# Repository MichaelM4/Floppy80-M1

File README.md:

########################################################################

Floppy 80 for the TRS-80 Model I

The Floppy80-M1 emulates the following features of the Expansion Interface
- 32k RAM expansion
- Up to 3 floppy drives
  - 1 and 2 sided
  - single and double density
  - up to 90 cylinders
- Up to 2 hard drives

Configuration of the Floppy80-M1 is performed with the placement of
files on the SD-Card inserted in its card reader.
The files are as follows:

system.cfg
- specifies system level options.  These are option that are not dependent
  of the ini file loaded.

  cfg options
  - Mem  - 0 = disable upper memory; 1 = enable upper memory;
           if not specified upper memory is enabled by default.
  - Wait - 0 = disable bus wait states; 1 = enable bus wait states.
           if not specified wait states are disabled by default.
  - Vhd  - 0 = disable hard disk emulation; 1 = enable hard disk emulation;
           if not specified hard disk emulation is enabled by default.

boot.cfg
- specified the default ini file to load at reset of the Floppy80
  when the floppy 80 boots or is reset it reads the contents of
  the boot.cfg to determine the default configuration ini file.

ini files
- specifies the disk images and options after reset.

  ini options
  - Drive0  - specified the image to load for drive :0
  - Drive1  - specified the image to load for drive :1
  - Drive2  - specified the image to load for drive :2
  - HD0     - specifies the image to load for tyhe first hard drive
  - HD1     - specifies the image to load for tyhe second hard drive
  - Doubler - 1 = doubler is enabled; 0 = doubler is disabled;

dmk files
- these are virtual disk images with a specific file format
  that allows them to be generated and used with a number
  of existing programs and simulators.

virtual hard drive images
- these are virtual hard drive images with a specific file format.
  They are used by the FreHD and TRS80-GP.

########################################################################

FDC utility
- Is a utility to interact with the Floppy80 from within the
  TRS-80 Model I operating environment.  Versions of FDC exist
  for the following operating systems

  - CPM 1.4.1 (Lifeboat)
  - CPM 1.5 (FMG)
  - Double DOS 4.2.4
  - DOS Plus 3.50
  - LDOS 5.3.1
  - MultiDOS 4.01
  - NEWDOS 3.0
  - NEWDOS 80 V2.0
  - TRSDOS 2.3
  - UltraDOS 4.2.0
  - VTDOS 3.0.0
  - VTDOS 4.0.1

  FDC.COM is used with the two CP/M OSs and
  FDC/CMD is used with the rest.

  Usage

  FDC OPT PARM1:drive

  Where:
  - OPT is one of the following
    - STA - returns the status of the Floppy80.
    - DIR - displays a list of file in the root folder of the SD-Card.
    - INI - switches between tyhe differnt ini file on the SD-Card.
    - DMK - allows the mounting of DMK disk images in the root folder
            of the SD-Card for a specified drive (0, 1 or 2).
    - FOR - copies a DMK disk image from the FOR folder of the SD-Card
            to one of the mounted disk images (0, 1 or 2).
    - IMP - imports a file from the root folder of the SD-Card
            into one of the mounted disk images (0, 1 or 2).

  FDC STA
  - Displays the contents to the ini file specified by boot.cfg

  FDC DIR filter
  - Displays a list of files in the root folder of the SD-Card.
    If filter is specified only files contain the filter character
    sequence are displayed.  If filter is not specified all files
    are displayed.

  FDC INI filename.exe
  - filename.exe is optional.  If not specified and list of ini files
    on the SD-Card will be displayed allow you to select the one to
    write to boot.cfg.  When specified FDC will bypass the file
    selection process.

  FDC DMK filename.exe n
  - filename.exe:n is optional.  When specified it will mount
    the dmk file names by filename.exe into the drive specified
    by n.  For example

    FDC DMK LDOS-DATA.DMK 2

    will mount the dmk file LDOS-DATA.DMK into drive :2

    If filename.exe:n is not specfied a list of dmk files
    will be listed allowing you to select on and the drive
    to mount it into.

  FDC FOR
  - list the files contained in the FMT folder of the SD-Card
    from which you can select one and specify the drive image
    to replace with it.  This is useful to generate blank disk
    images.

  FDC IMP filename.exe:n
  - imports the specified file from the root folder of the
    FAT32 formatted SD-Card to the disk image indicated by n.

########################################################################

Building Source
- Floppy80 firmware
  - Uses VSCode and the Pi Pico extension.

- FDC TRS (utility for the TRSDOS related utility)
  
  - zmac fdc.asm
  - use TRS80GP to import FDC/CMD onto a disk image
    
    - trs80gp -m1 -vs -frehd -frehd_dir zout -turbo -mem 48 -d0 dmk\ld531-0.dmk -d1 dmk\ld531-1.dmk -i "IMPORT2 FDC.CMD FDC/CMD:1\r"

- FDC CP/M (utility for the CP/M related utility)
  1. Compile program into a hex file.
  
       zmac fdc.asm
     
  2. Run TRS80GP loading the CP/M disk images.
     
       start trs80gp -m1 -vs -frehd -frehd_dir zout -turbo -mem 48 -d0 CPM141-0.dmk -d1 CPM141-1.dmk -d2 CPM141-2.dmk
     
  3. Select Load from TRS80GP File menu and select the hex file.
  
  4. Run "SAVE 20 B:FDC.COM" to save program memory contents to a .com file.
     As the program grows you will need to increase the value after SAVE.

     SAVE n ufn cr
     
       n   - number of 256-byte pages to be saved.
     
       ufn - unambiguous file name.
     
       cr  - carriage return.

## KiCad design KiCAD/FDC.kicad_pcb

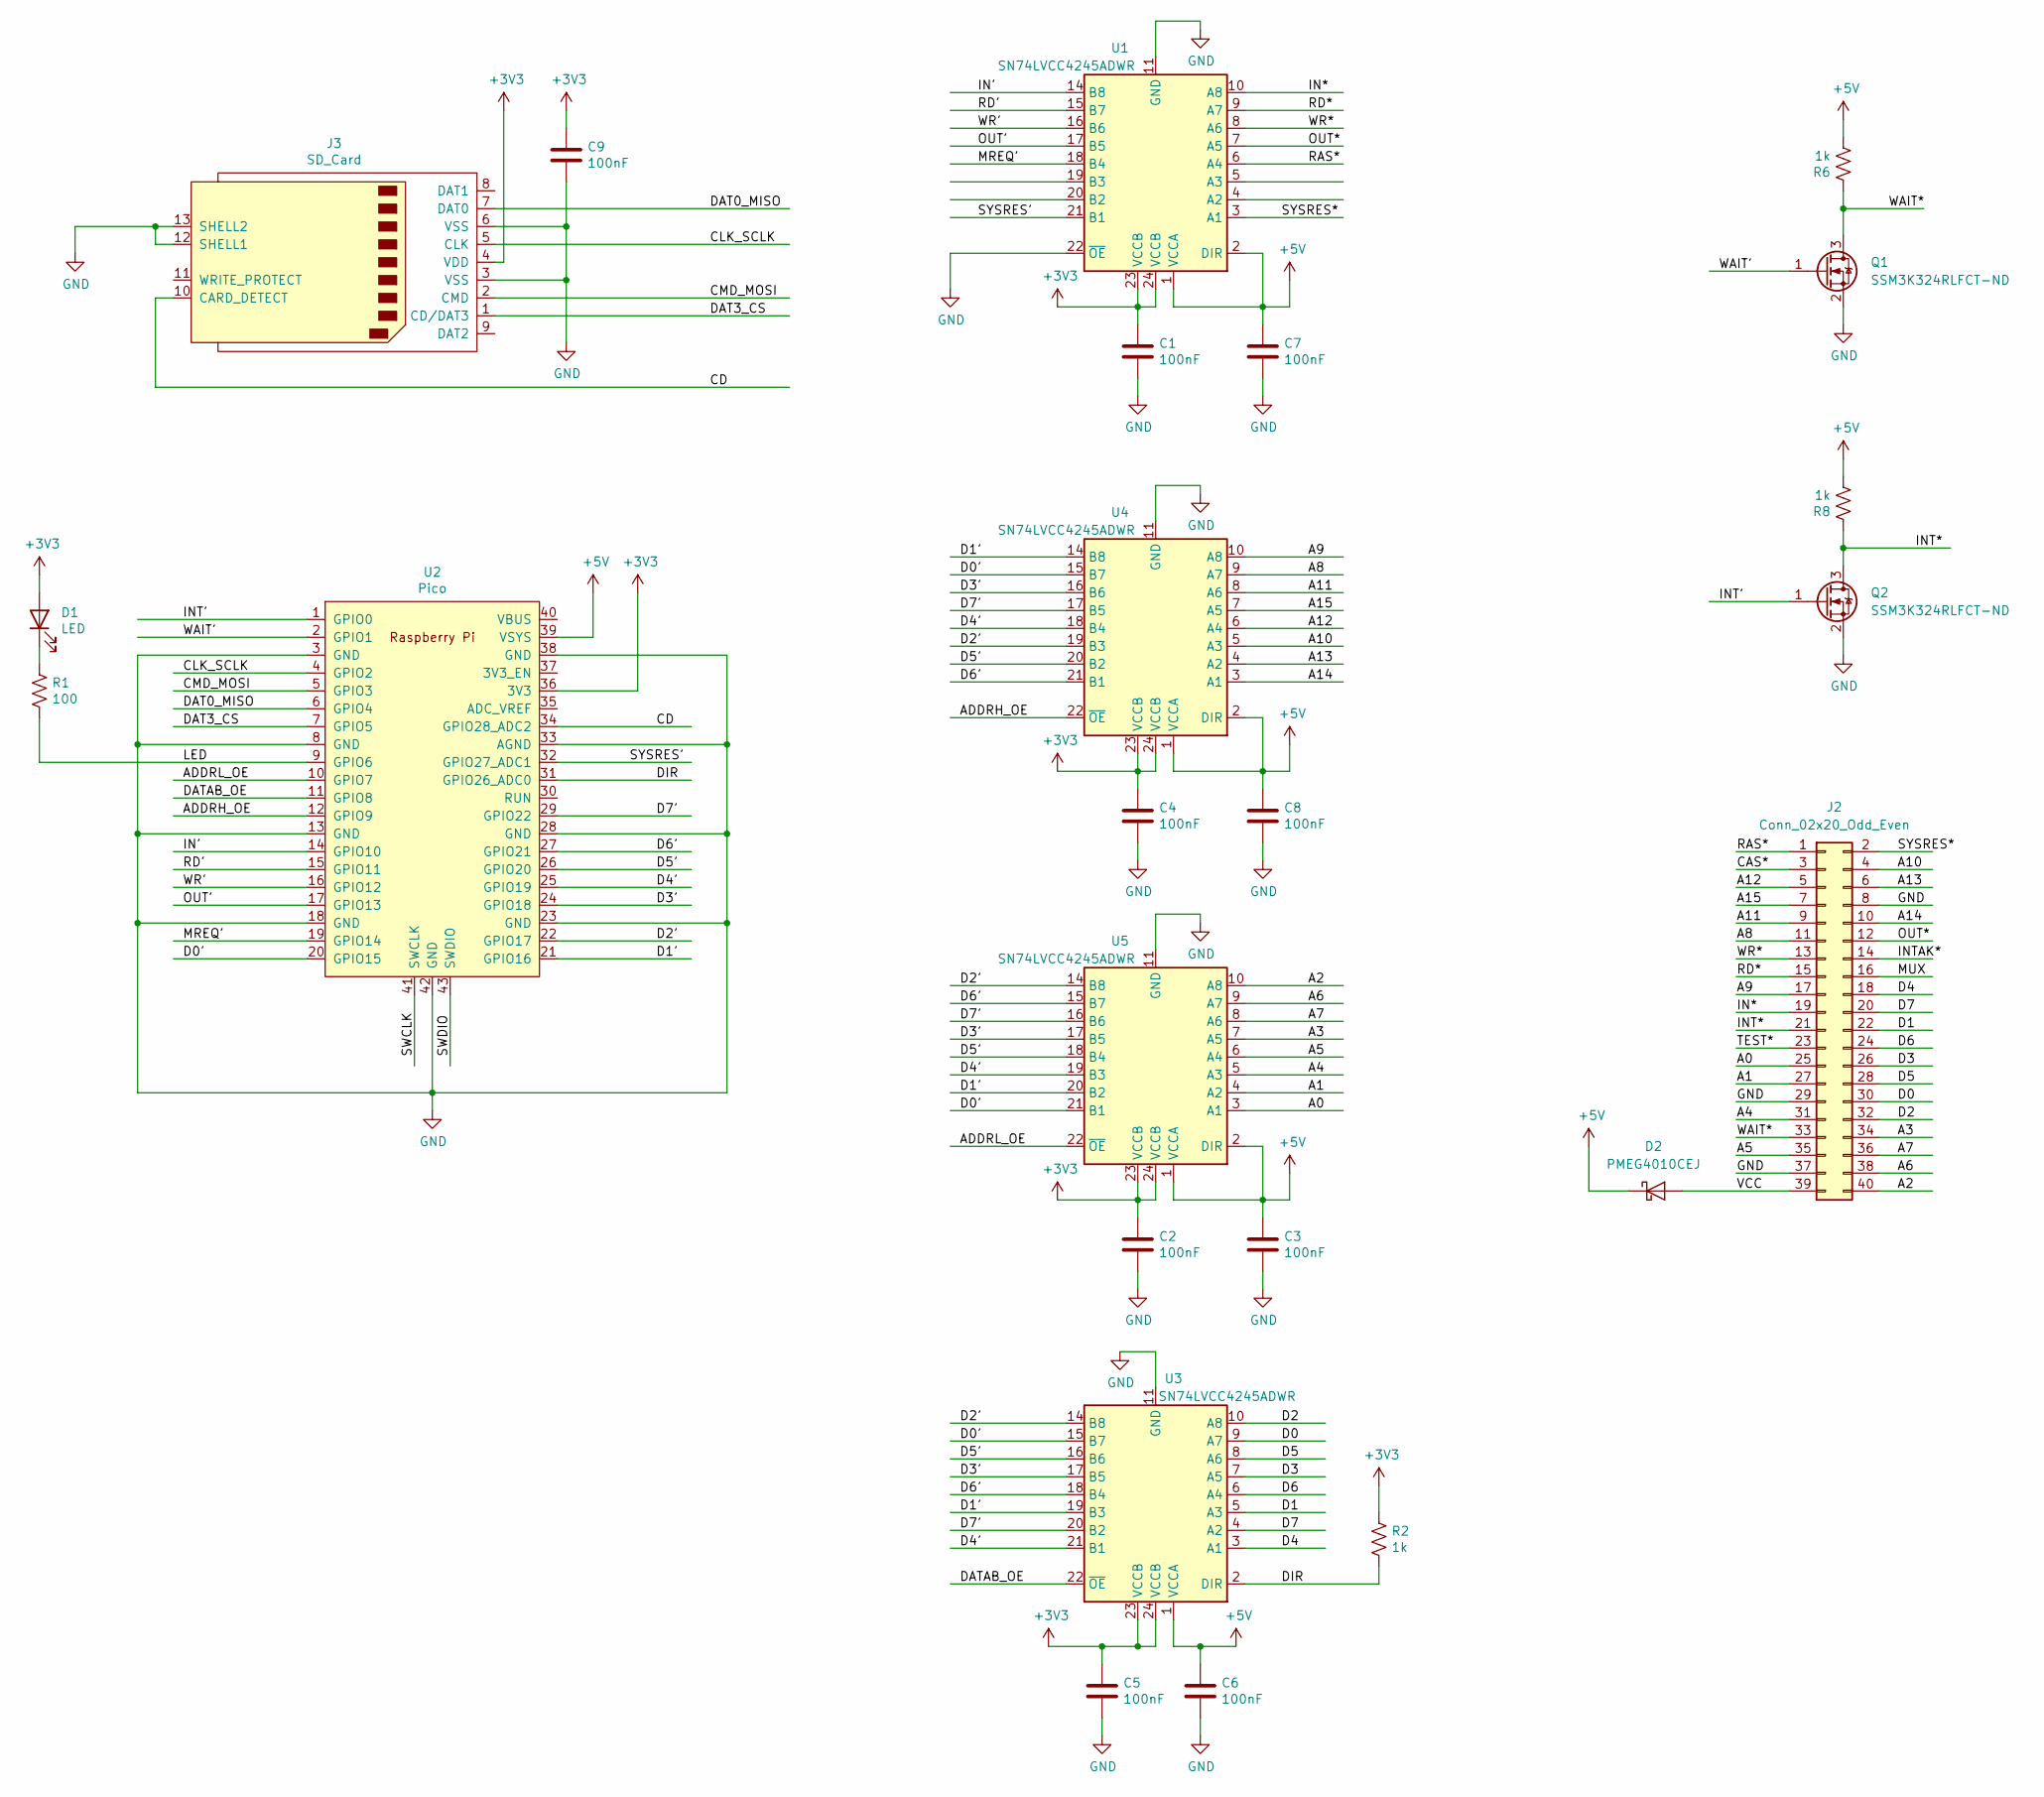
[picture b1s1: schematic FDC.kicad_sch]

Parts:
C1, C2, C3, C4, C5, C6, C7, C8, C9: 100nF; C_0805_2012Metric_Pad1.18x1.45mm_HandSolder; Digikey 732-8080-1-ND
D1: LED; LED_2816_7142Metric_Pad3.20x4.45mm_HandSolder; Digikey 754-1519-1-ND
D2: PMEG4010CEJ; D_SOD-323F
J2: Conn_02x20_Odd_Even; PinSocket_2x20_P2.54mm_Vertical; Part A31723-ND; Digikey A31723-ND
J3: SD_Card; SD_Kyocera_145638009511859+; Digikey 609-3956-1-ND
Q1, Q2: SSM3K324RLFCT-ND; SOT-23_Handsoldering; Digikey SSM3K324RLFCT-ND
R1: 100; R_0805_2012Metric_Pad1.20x1.40mm_HandSolder; Digikey RMCF0805FT100RCT-ND
R2, R6, R8: 1k; R_0805_2012Metric_Pad1.20x1.40mm_HandSolder; Digikey A106056CT-ND
U1, U3, U4, U5: SN74LVCC4245ADWR; SOIC-24W_7.5x15.4mm_P1.27mm; Digikey 296-26634-1-ND
U2: Pico; RPi_Pico_SMD_TH; Digikey 2648-SC0915CT-ND

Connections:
+3V3: C1.1, C2.1, C4.1, C5.1, C9.1, D1.2 (A), J3.4 (VDD), R2.1, U1.23 (VCCB), U1.24 (VCCB), U2.36 (3V3), U3.23 (VCCB), U3.24 (VCCB), U4.23 (VCCB), U4.24 (VCCB), U5.23 (VCCB), U5.24 (VCCB)
+5V: C3.1, C6.1, C7.1, C8.1, D2.1 (K), R6.2, R8.2, U1.1 (VCCA), U1.2 (DIR), U2.39 (VSYS), U3.1 (VCCA), U4.1 (VCCA), U4.2 (DIR), U5.1 (VCCA), U5.2 (DIR)
/A0: J2.25, U5.3 (A1)
/A1: J2.27, U5.4 (A2)
/A2: J2.40, U5.10 (A8)
/A3: J2.34, U5.7 (A5)
/A4: J2.31, U5.5 (A3)
/A5: J2.35, U5.6 (A4)
/A6: J2.38, U5.9 (A7)
/A7: J2.36, U5.8 (A6)
/A8: J2.11, U4.9 (A7)
/A9: J2.17, U4.10 (A8)
/A10: J2.4, U4.5 (A3)
/A11: J2.9, U4.8 (A6)
/A12: J2.5, U4.6 (A4)
/A13: J2.6, U4.4 (A2)
/A14: J2.10, U4.3 (A1)
/A15: J2.7, U4.7 (A5)
/ADDRH_OE: U2.12 (GPIO9), U4.22 (~OE)
/ADDRL_OE: U2.10 (GPIO7), U5.22 (~OE)
/CAS*: J2.3
/CD: J3.10 (CARD_DETECT), U2.34 (GPIO28_ADC2)
/CLK_SCLK: J3.5 (CLK), U2.4 (GPIO2)
/CMD_MOSI: J3.2 (CMD), U2.5 (GPIO3)
/D0: J2.30, U3.9 (A7)
/D0': U2.20 (GPIO15), U3.15 (B7), U4.15 (B7), U5.21 (B1)
/D1: J2.22, U3.5 (A3)
/D1': U2.21 (GPIO16), U3.19 (B3), U4.14 (B8), U5.20 (B2)
/D2: J2.32, U3.10 (A8)
/D2': U2.22 (GPIO17), U3.14 (B8), U4.19 (B3), U5.14 (B8)
/D3: J2.26, U3.7 (A5)
/D3': U2.24 (GPIO18), U3.17 (B5), U4.16 (B6), U5.17 (B5)
/D4: J2.18, U3.3 (A1)
/D4': U2.25 (GPIO19), U3.21 (B1), U4.18 (B4), U5.19 (B3)
/D5: J2.28, U3.8 (A6)
/D5': U2.26 (GPIO20), U3.16 (B6), U4.20 (B2), U5.18 (B4)
/D6: J2.24, U3.6 (A4)
/D6': U2.27 (GPIO21), U3.18 (B4), U4.21 (B1), U5.15 (B7)
/D7: J2.20, U3.4 (A2)
/D7': U2.29 (GPIO22), U3.20 (B2), U4.17 (B5), U5.16 (B6)
/DAT0_MISO: J3.7 (DAT0), U2.6 (GPIO4)
/DAT3_CS: J3.1 (CD/DAT3), U2.7 (GPIO5)
/DATAB_OE: U2.11 (GPIO8), U3.22 (~OE)
/DIR: R2.2, U2.31 (GPIO26_ADC0), U3.2 (DIR)
/IN': U1.14 (B8), U2.14 (GPIO10)
/IN*: J2.19, U1.10 (A8)
/INT': Q2.1 (G), U2.1 (GPIO0)
/INT*: J2.21, Q2.3 (D), R8.1
/INTAK*: J2.14
/LED: R1.2, U2.9 (GPIO6)
/MREQ': U1.18 (B4), U2.19 (GPIO14)
/MUX: J2.16
/OUT': U1.17 (B5), U2.17 (GPIO13)
/OUT*: J2.12, U1.7 (A5)
/RAS*: J2.1, U1.6 (A4)
/RD': U1.15 (B7), U2.15 (GPIO11)
/RD*: J2.15, U1.9 (A7)
/SWCLK: U2.41 (SWCLK)
/SWDIO: U2.43 (SWDIO)
/SYSRES': U1.21 (B1), U2.32 (GPIO27_ADC1)
/SYSRES*: J2.2, U1.3 (A1)
/TEST*: J2.23
/VCC: D2.2 (A), J2.39
/WAIT': Q1.1 (G), U2.2 (GPIO1)
/WAIT*: J2.33, Q1.3 (D), R6.1
/WR': U1.16 (B6), U2.16 (GPIO12)
/WR*: J2.13, U1.8 (A6)
GND: C1.2, C2.2, C3.2, C4.2, C5.2, C6.2, C7.2, C8.2, C9.2, J2.8, J2.29, J2.37, J3.3 (VSS), J3.6 (VSS), J3.12 (SHELL1), J3.13 (SHELL2), Q1.2 (S), Q2.2 (S), U1.11 (GND), U1.12 (GND), U1.13 (GND), U1.22 (~OE), U2.3 (GND), U2.8 (GND), U2.13 (GND), U2.18 (GND), U2.23 (GND), U2.28 (GND), U2.33 (AGND), U2.38 (GND), U2.42 (GND), U3.11 (GND), U3.12 (GND), U3.13 (GND), U4.11 (GND), U4.12 (GND), U4.13 (GND), U5.11 (GND), U5.12 (GND), U5.13 (GND)
unnamed: D1.1 (K), R1.1

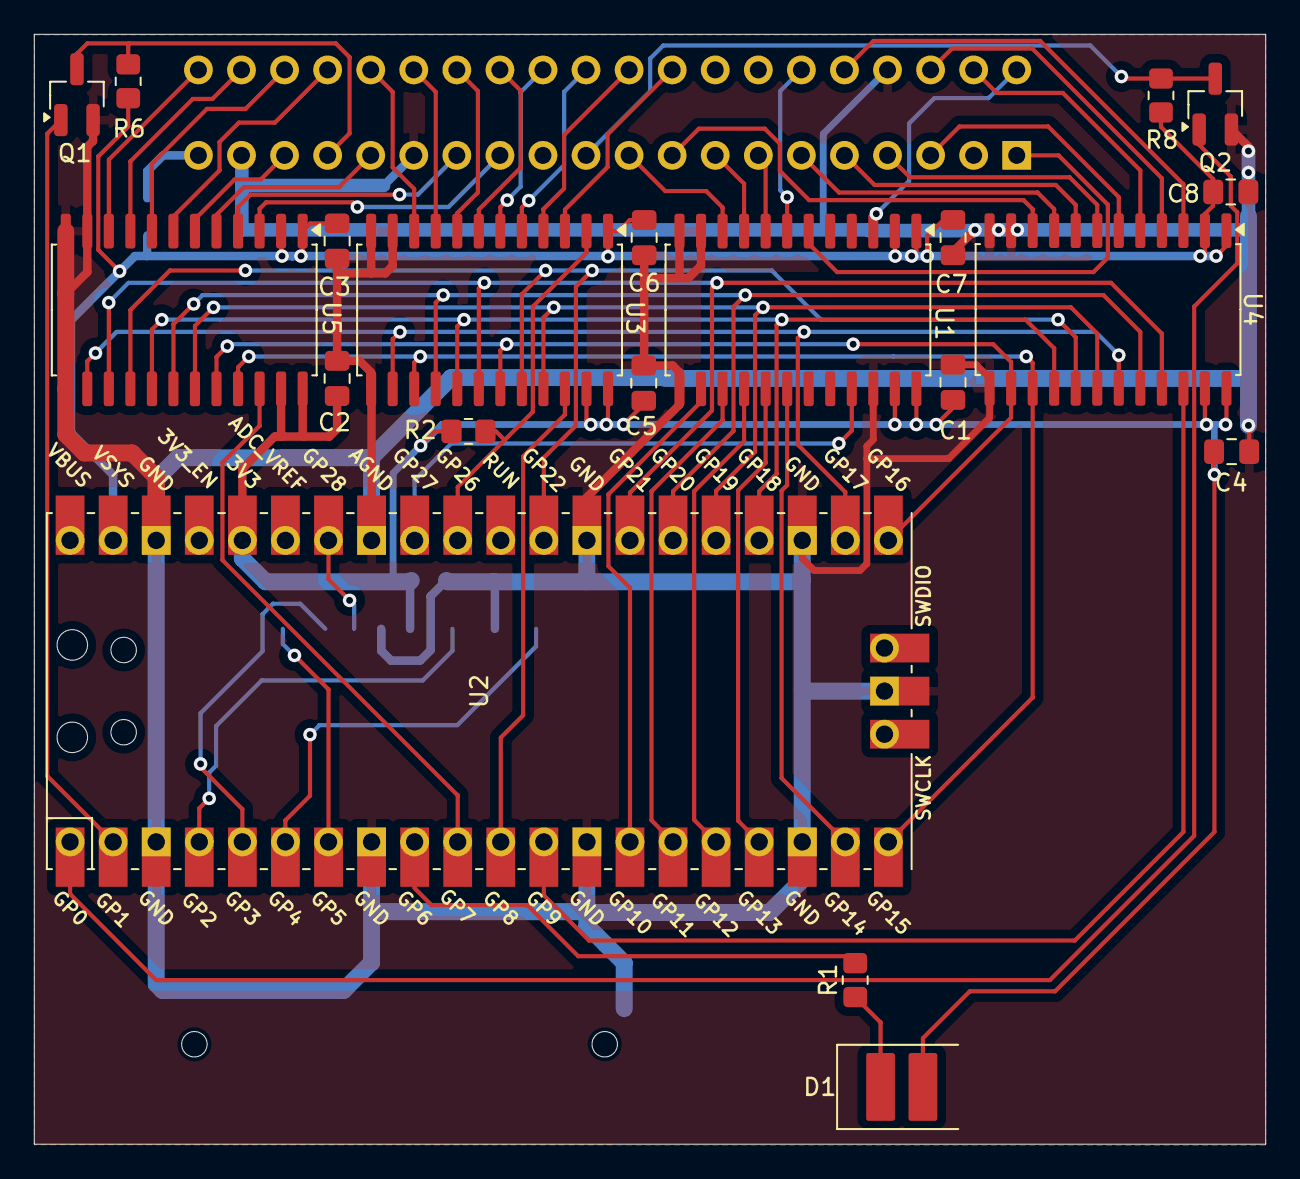
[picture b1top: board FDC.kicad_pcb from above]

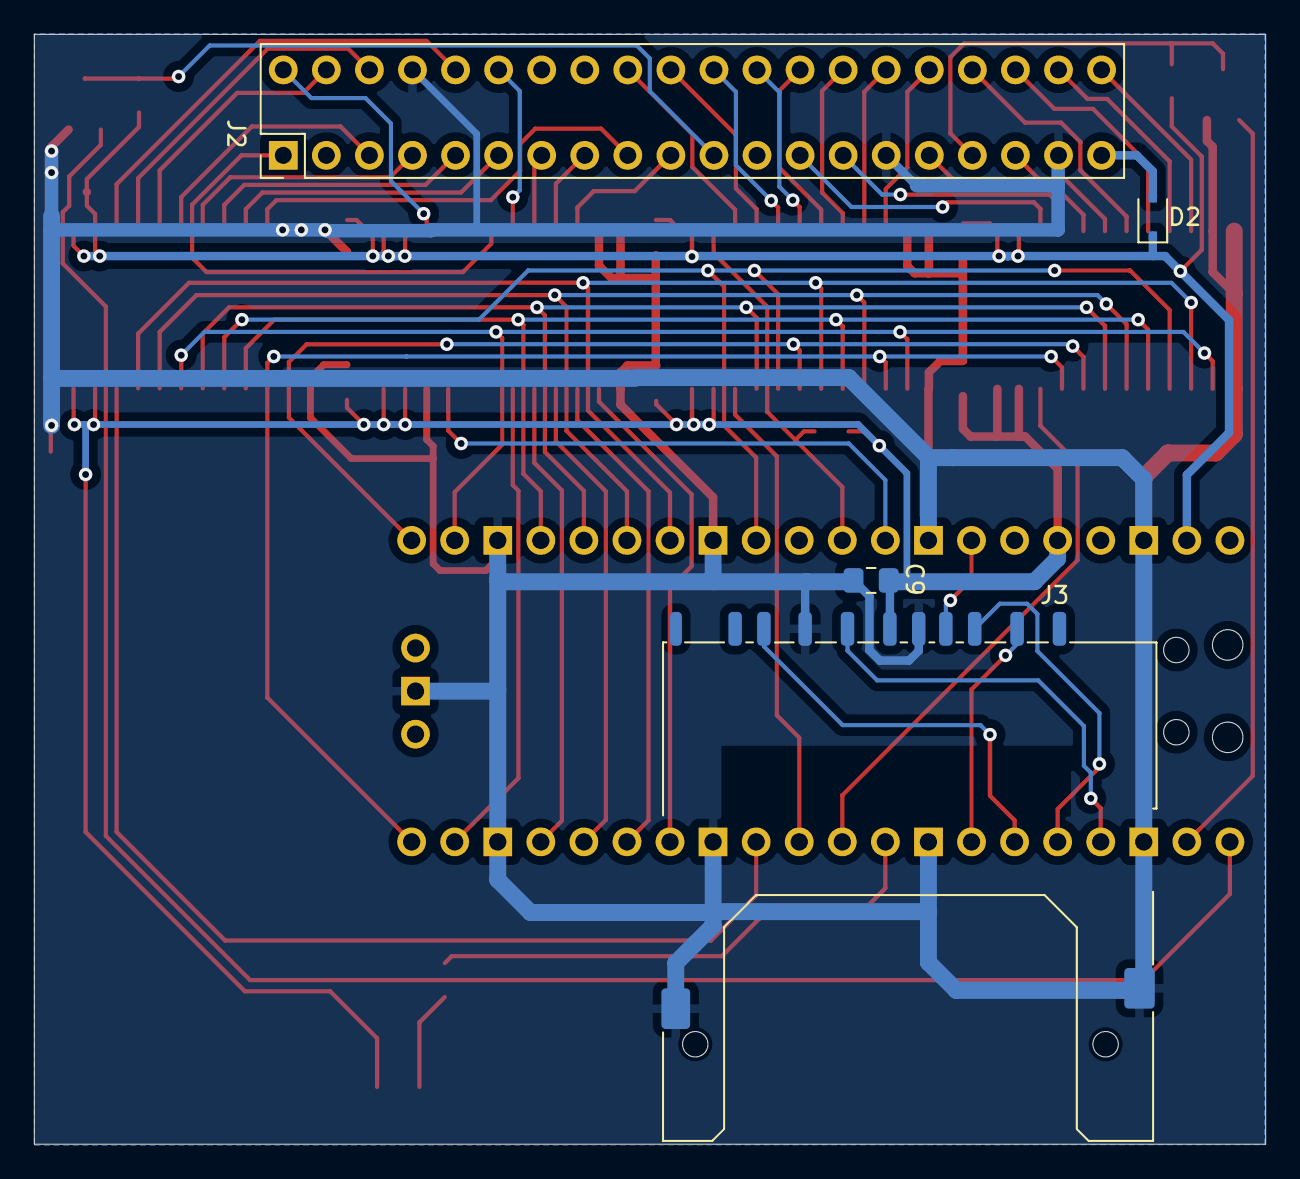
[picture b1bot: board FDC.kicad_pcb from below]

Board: 2 copper layers, 72.6 x 65.5 mm, 24 parts (4 on the bottom side), 63 nets.

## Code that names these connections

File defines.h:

#ifndef _H_DEFINES_
#define _H_DEFINES_

#define ENABLE_DOUBLER 1
#define ENABLE_LOGGING 1

//#pragma GCC optimize ("O0")
#pragma GCC optimize ("O3")

#include <stdio.h>

#define CDC_ITF     0           /* USB CDC interface no */

typedef signed char        	int8_t;
typedef unsigned char		uint8_t;
typedef short              	int16_t;
typedef unsigned short     	uint16_t;
typedef long               	int32_t;
typedef unsigned long      	uint32_t;
typedef long long          	int64_t;
typedef unsigned long long 	uint64_t;

typedef unsigned char		byte;
typedef unsigned short     	word;
typedef unsigned long      	dword;

#define SizeOfArray(x) (sizeof(x) / sizeof(x[0]))

// set to 1 to enable capture of bus activity logging to sd-card
#define ENABLE_TRACE_LOG 0

#define INT_PIN       0
#define WAIT_PIN      1
#define CLK_SCLK      2
#define CMD_MOSI      3

#define DAT0_MISO     4
#define DAT3_CS       5
#define LED_PIN       6
#define ADDRL_OE_PIN  7

#define DATAB_OE_PIN  8
#define ADDRH_OE_PIN  9
#define IN_PIN        10
#define RD_PIN        11

#define WR_PIN        12
#define OUT_PIN       13
#define MREQ_PIN      14
#define D0_PIN        15

#define D1_PIN        16
#define D2_PIN        17
#define D3_PIN        18
#define D4_PIN        19

#define D5_PIN        20
#define D6_PIN        21
#define D7_PIN        22

#define DIR_PIN       26
#define SYSRES_PIN    27
#define CD_PIN        28

// Bit  Net      Input    Hex
//             (1=input)
// 31    -         0
// 30    -         0
// 29    -         0
// 28    CD        1       1     0
//
// 27    SYSRES    1
// 26    DIR       0
// 25    -         0
// 24    -         0       8     0
//
// 23    -         0
// 22    D7        1
// 21    D6        1
// 20    D5        1       7     7
//
// 19    D4        1
// 18    D3        1
// 17    D2        1
// 16    D1        1       F     F
//
// 15    D0        1
// 14    RAS       1
// 13    OUT       1
// 12    WR        1       F     8
//
// 11    RD        1
// 10    IN        1
//  9    ADDRH     0
//  8    DATAB     0       C     0
//
//  7    ADDRL     0
//  6    LED       0
//  5    DAT3_CS   0
//  4    DAT0_MISO 0       0     0
//
//  3    CMD_MOSI  0
//  2    CLK_SCLK  0
//  1    WAIT      0
//  0    INT       0       0     0

#define GPIO_IN_MASK  0x187FFC00
#define DATA_BUS_MASK 0x007F8000

#define A_TO_B_DIR 1
#define B_TO_A_DIR 0

///////////////////////////////////////////////////////////////////////////////////////////////////

#define get_gpio_data_byte() (sio_hw->gpio_in >> D0_PIN)
#define get_gpio_read_bus()  (sio_hw->gpio_in >> IN_PIN)
#define get_gpio(gpio)       (sio_hw->gpio_in & (1u << gpio))
#define set_gpio(gpio)        sio_hw->gpio_set = 1u << gpio
#define clr_gpio(gpio)        sio_hw->gpio_clr = 1u << gpio
#define set_bus_as_output()   sio_hw->gpio_oe_set = 0xFF << D0_PIN
#define set_bus_as_input()    sio_hw->gpio_oe_clr = 0xFF << D0_PIN
#define put_byte_on_bus(data) sio_hw->gpio_togl = (sio_hw->gpio_out ^ (data << D0_PIN)) & (0xFF << D0_PIN)

// #define get_gpio_data_byte()  gpio_get_all() >> D0_PIN
// #define get_gpio(gpio)        gpio_get(gpio)
// #define set_gpio(gpio)        gpio_put(gpio, 1)
// #define clr_gpio(gpio)        gpio_put(gpio, 0)
// #define set_bus_as_output()   gpio_set_dir_out_masked(0xFF << D0_PIN)
// #define set_bus_as_input()    gpio_set_dir_in_masked(0xFF << D0_PIN)
// #define put_byte_on_bus(data) gpio_put_masked(0xFF << D0_PIN, data << D0_PIN)

///////////////////////////////////////////////////////////////////////////////////////////////////

// Low Power Timer Overflow Rates in Hz
#define TIMER_OVERFLOW_RATE 2000

///////////////////////////////////////////////////////////////////////////////////////////////////
// generic defines/equates

#ifndef TRUE
	#define FALSE	0
	#define TRUE	1
#endif

#ifndef true
	#define false	0
	#define true	1
#endif

#ifndef MAX_PATH
  #define MAX_PATH 64
#endif

///////////////////////////////////////////////////////////////////////////////////////////////////
// FDC logging

typedef struct {
	uint8_t type;
	uint8_t val;
	uint8_t op1;
} LogType;

#define LOG_SIZE 4096

extern LogType fdc_log[LOG_SIZE];
extern int log_head;
extern int log_tail;

enum {
	write_drive_select = 0,
	write_data,
	write_sector,
	write_track,
	write_cmd,
	read_drive_select,
	read_data,
	read_sector,
	read_track,
	read_status,
	port_out,
	port_in
};

///////////////////////////////////////////////////////////////////////////////////////////////////
// typedefs

typedef struct {
   uint64_t nSectorsTotal;
   uint64_t nSectorsFree;
   uint64_t nSectorSize;

   uint32_t nClustersTotal;
   uint32_t nClustersFree;
   uint32_t nClustersUsed;
   uint32_t nClustersBad;
   uint32_t nClusterSize;
} F_SPACE;

///////////////////////////////////////////////////////////////////////////////////////////////////
// enumerations

enum {
  opRead = 0,
  opWrite,
  opNop
};

///////////////////////////////////////////////////////////////////////////////////////////////////
// global variables

//-----------------------------------------------------------------------------
// counter for real time clock (RTC).

extern volatile uint8_t sd_byCardInialized;
extern volatile byte    g_byFdcIntrActive;
extern volatile byte    g_byRtcIntrActive;
extern volatile byte    g_byResetActive;
extern volatile byte    g_byEnableIntr;
extern volatile int32_t g_nRotationCount;

///////////////////////////////////////////////////////////////////////////////////////////////////

void InitVars(void);
void ReleaseWait(void);

byte* TD230_GetPtr(void);
int   TD230_Size(void);

///////////////////////////////////////////////////////////////////////////////////////////////////

#endif

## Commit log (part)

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2024-10-10 Recognizes disk system.
2024-10-11 Turns off logging and adds LED control.
2024-10-11 Code cleanup
2024-10-12 Output video memory to the USB CDC port. Using VT100 codes.
2024-10-12 Simplified logging.
2024-10-13 Simplifies CDC checking.
2024-10-13 Removed irrelevant code.
2024-10-14 Add support for the STA and INI (FDC commands). Model 1 supports only 3 drives.
2024-10-14 Adds FDC/CMD source compatible with Floppy80-M1`
2024-10-21 Adds support for double byte data in sectors.
2024-10-21 Bumped version and improved speed.
2024-10-22 Minor cleanup.
2024-10-22 Subdivided service_memory() into additional functions.
2024-10-25 Verifies that the specified ini boot file exists.
2024-10-26 Increased speed
2024-10-26 Restructured for speed.
2024-10-27 Waits 2 (2000000u) seconds before accessing stdio.
2024-10-27 Changes the message after mounting and ini file.
2024-10-27 Removed video shadow memory.
2024-10-27 Corrected comments for WD1771 data sheet.
2024-11-01 Conditional compilation base on processor (pico or pico 2).
2024-11-06 Enable pull up for CD input.
2024-11-08 Adds a state timer the the FDC state machine to replace the state counter.
2024-11-12 Removed wait state for reading FDC status register.
2024-11-12 Reverting to earlier code.
2024-11-14 Adds support for the dmk format operation.
2024-11-15 Changes the disk label for the TRSDOS 2.3 disk image to TD230.
2024-11-23 Adjusts density based on track data.
2024-12-22 Disable motor speed tests.
2024-12-22 Updates to latest SDK
2024-12-22 Fixes for TRSDOS 2.3 Format prorgram.
2024-12-22 More code to string changes.
2024-12-22 More string definitions.
2024-12-25 Code compatibility between the two environments using fdc.c
2024-12-28 More changes
2024-12-29 Sets write length based on density (single vs double).
2025-09-22 Updated comments
2025-09-22 Adds drive status for faster reads.
2025-09-22 Removed wait states from memory and drive read/writes.
2025-09-25 Activates LED while the format/copy disk image runs.
2025-09-27 Adds formatting and copying support for DOS Plus 3.50
2025-09-29 Increase log buffer size
2025-09-30 Included file size in dir listing.
2025-09-30 Adds file operation for truncating a file.
2025-09-30 Adds code to set data lost flag if data register is not read within 1ms
2025-09-30 Density is now determined when the track is written
2025-10-02 Adds logging information for drive doublers.
2025-10-03 Once a doubler model has been selected the other can not be enabled until the controller is reset.
2025-10-06 Adds support for FDC IMP operation.
2025-10-12 Adds support for the FDC VGA board.
2025-10-13 Resolves real-time update failure "TIME (CLOCK+ON)"
2025-10-13 Comments
2025-10-15 Removes the drive selection prompt for INI request.
2025-10-15 Added file for HDC operations and servicing of port I/O
2025-10-16 Implementation of HD controller registers.
2025-10-16 Improved debug logging
2025-10-17 Mode changes.
2025-10-21 BACKUP/CMD issue resolved.
2025-10-24 Simplified
2025-10-31 Increases performance to remove need for wait states
2025-11-07 Lost in merge with main
2025-11-07 Update to the KiCAD folder
2025-11-15 Moves request/response memory region to start at address 0x3400 and reduces the size of each to 0x110 bytes.
2025-11-15 Updated CP/M version of FDC.COM
2025-11-27 Moved firmware source to its own folder
2025-11-27 moved readme md back to root of project
2025-11-28 Adds MEM ini option to enable/disable upper 32k memory support.
2025-11-29 Adds an ini option to enable wait states for systems with higher clocks.
2025-11-30 Moved MEM and WAIT options to a system level configuration file (system.cfg).
2025-12-04 User Guide
2025-12-06 improved docs
2025-12-06 Adds a configuration option to disable hard disk emulation.
2025-12-06 Replace ' ' in folder names with '_'
2025-12-17 Removes backup folder and adds PCB and BOM files
